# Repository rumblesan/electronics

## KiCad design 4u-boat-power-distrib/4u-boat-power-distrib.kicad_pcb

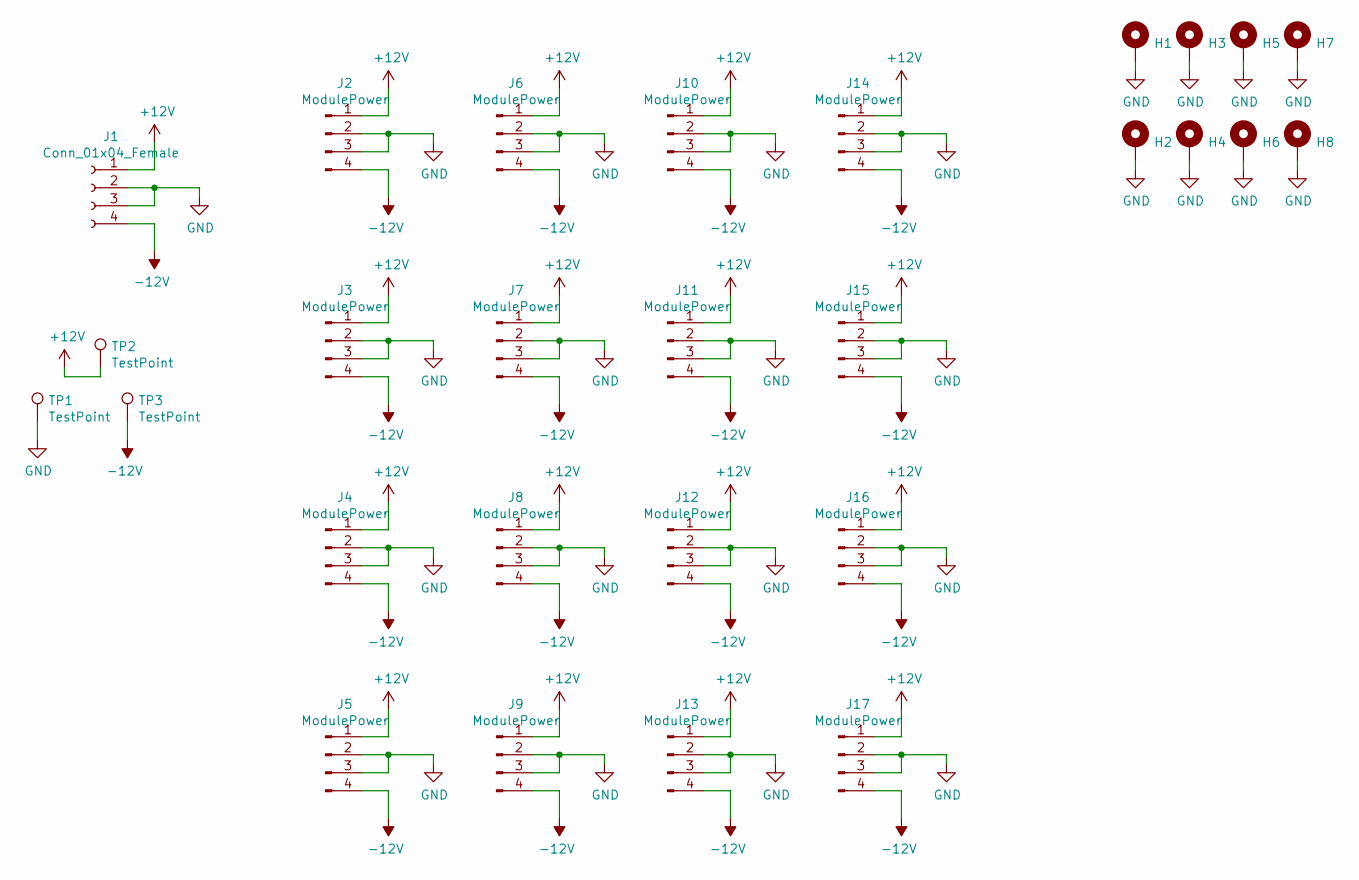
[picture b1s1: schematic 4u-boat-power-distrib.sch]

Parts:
H1, H2, H3, H4, H5, H6, H7, H8: MountingHole_Pad; MountingHole_3.2mm_M3_DIN965_Pad
J1: Conn_01x04_Female; PowerConnection-SolderWire-0.75sqmm_1x04_P4.8mm_D1.25mm_OD2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
J2, J3, J4, J5, J6, J7, J8, J9, J10, J11, J12, J13, J14, J15, J16, J17: ModulePower; KK396_RightAngle_01x04
TP1, TP2, TP3: TestPoint; TestPoint_Loop_D1.80mm_Drill1.0mm_Beaded

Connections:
+12V: J1.1, J2.1, J3.1, J4.1, J5.1, J6.1, J7.1, J8.1, J9.1, J10.1, J11.1, J12.1, J13.1, J14.1, J15.1, J16.1, J17.1, TP2.1
-12V: J1.4, J2.4, J3.4, J4.4, J5.4, J6.4, J7.4, J8.4, J9.4, J10.4, J11.4, J12.4, J13.4, J14.4, J15.4, J16.4, J17.4, TP3.1
GND: H1.1, H2.1, H3.1, H4.1, H5.1, H6.1, H7.1, H8.1, J1.2, J1.3, J2.2, J2.3, J3.2, J3.3, J4.2, J4.3, J5.2, J5.3, J6.2, J6.3, J7.2, J7.3, J8.2, J8.3, J9.2, J9.3, J10.2, J10.3, J11.2, J11.3, J12.2, J12.3, J13.2, J13.3, J14.2, J14.3, J15.2, J15.3, J16.2, J16.3, J17.2, J17.3, TP1.1

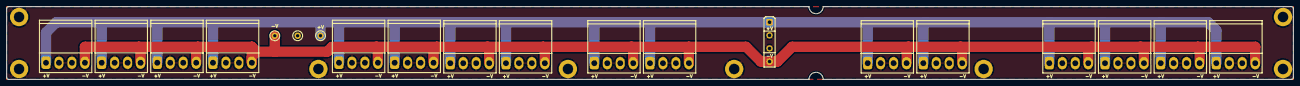
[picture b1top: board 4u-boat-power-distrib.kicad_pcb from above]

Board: 2 copper layers, 393.1 x 22.2 mm, 28 parts (0 on the bottom side), 3 nets.

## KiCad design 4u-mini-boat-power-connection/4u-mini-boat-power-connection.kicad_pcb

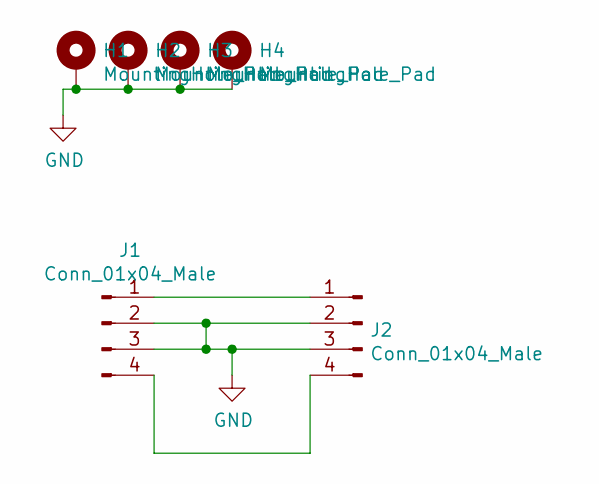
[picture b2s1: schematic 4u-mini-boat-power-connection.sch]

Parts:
H1, H2, H3, H4: MountingHole_Pad; MountingHole_3.2mm_M3_Pad
J1: Conn_01x04_Male; TE_FASTON_250_1217754-1_1x04_P5.08mm_Horizontal
J2: Conn_01x04_Male; Molex_KK-254_AE-6410-04A_1x04_P2.54mm_Vertical

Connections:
GND: H1.1, H2.1, H3.1, H4.1, J1.2, J1.3, J2.2, J2.3
unnamed: J1.1, J2.1
unnamed: J1.4, J2.4

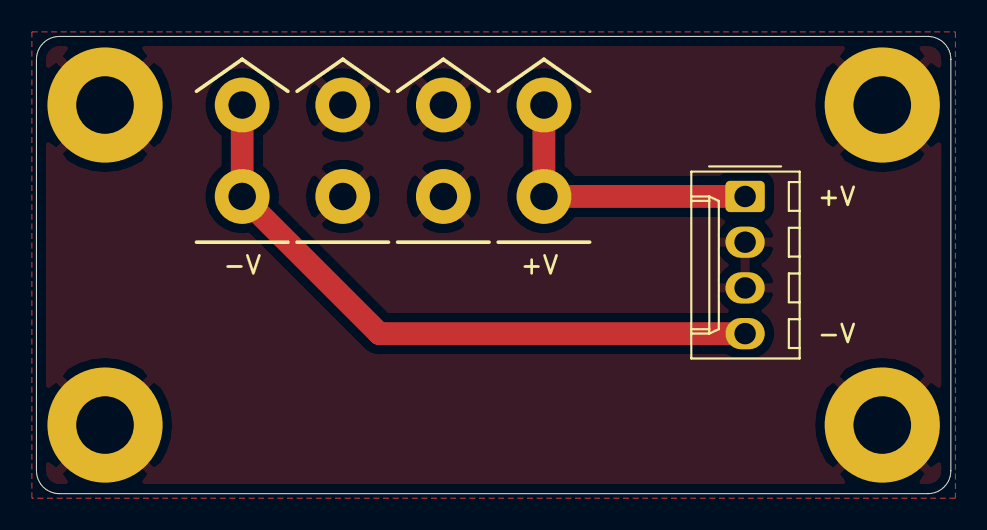
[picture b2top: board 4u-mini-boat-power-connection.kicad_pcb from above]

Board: 2 copper layers, 50.8 x 25.4 mm, 6 parts (0 on the bottom side), 3 nets.

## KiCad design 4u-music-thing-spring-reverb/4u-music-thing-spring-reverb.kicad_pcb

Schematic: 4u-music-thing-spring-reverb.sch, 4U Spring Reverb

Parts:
C1, C2, C10, C12, C13: 10uf; CP_Radial_D5.0mm_P2.50mm
C3: 22uf; CP_Radial_D6.3mm_P2.50mm
C4: 2.2nf; C_Rect_L7.0mm_W2.5mm_P5.00mm
C5, C8, C9: 22pf; C_Rect_L7.0mm_W2.5mm_P5.00mm
C6, C7: 33nf; C_Rect_L7.0mm_W2.5mm_P5.00mm
C11: 3n3f; C_Rect_L7.0mm_W2.5mm_P5.00mm
C14, C15, C16, C17, C18, C19: 100nf; C_Rect_L7.0mm_W2.5mm_P5.00mm
D1, D2: 1n4004; Diode_THT_P7.62mm_Horizontal
J1: IN1; BananaJack_THT_JohnsonCinch_108-09
J2: REV_RETURN; SolderWire-24AWG-0.2sqmm_1x02_D0.5mm_OD1.1mm_Relief
J3: IN2; BananaJack_THT_JohnsonCinch_108-09
J4: OUT; BananaJack_THT_JohnsonCinch_108-09
J5: REV_SEND; SolderWire-24AWG-0.2sqmm_1x02_D0.5mm_OD1.1mm_Relief
J6: TILT_MAIN; PinSocket_1x03_P2.54mm_Vertical
J7: TILT_CTRL; PinHeader_1x03_P2.54mm_Vertical
J8: Conn_01x04_Male; Molex_KK-254_AE-6410-04A_1x04_P2.54mm_Vertical
J9: MIX_CTRL; PinHeader_1x03_P2.54mm_Vertical
J10: MIX_MAIN; PinSocket_1x03_P2.54mm_Vertical
J11: AUDIO_IO_MAIN; PinSocket_1x04_P2.54mm_Vertical
J12: AUDIO_IO_CTRL; PinHeader_1x04_P2.54mm_Vertical
R1: 4k7; Resistor_THT_L6.3mm_D2.5mm_P10.16mm_Horizontal
R2: 22r; Resistor_THT_L6.3mm_D2.5mm_P10.16mm_Horizontal
R3: 22k; Resistor_THT_L6.3mm_D2.5mm_P10.16mm_Horizontal
R4, R5, R6: 10k; Resistor_THT_L6.3mm_D2.5mm_P10.16mm_Horizontal
R7, R12, R15: 2k2; Resistor_THT_L6.3mm_D2.5mm_P10.16mm_Horizontal
R8, R11: 6k8; Resistor_THT_L6.3mm_D2.5mm_P10.16mm_Horizontal
R9, R10, R16: 100k; Resistor_THT_L6.3mm_D2.5mm_P10.16mm_Horizontal
R13: 330; Resistor_THT_L6.3mm_D2.5mm_P10.16mm_Horizontal
R14: 10k; Potentiometer_THT_Bourns_3306P_Vertical
RV1, RV2: 100k; Potentiometer_Alpha_RD901F-40-00D_Single_Vertical
RV3: 10k; Potentiometer_Alpha_RD901F-40-00D_Single_Vertical
U1, U3: TL072; DIP-8_W7.62mm_Socket
U2: NE5532; DIP-8_W7.62mm_Socket

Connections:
+12V: C12.1, C14.1, C16.1, C18.1, D1.1, U1.8 (V+), U2.8 (V+), U3.8 (V+)
-12V: C13.2, C15.2, C17.2, C19.2, D2.2, U1.4 (V-), U2.4 (V-), U3.4 (V-)
/AUDIO1_IN_CTRL: J12.2, RV1.2
/AUDIO1_IN_MAIN: J11.2, R5.2
/AUDIO2_IN_CTRL: C2.1, J12.3, R16.1
/AUDIO2_IN_MAIN: J11.3, R4.2
/AUDIO_DRY_CTRL: J9.1, RV2.1
/AUDIO_DRY_MAIN: J10.1, U3.1, U3.2 (-)
/AUDIO_MIX: C5.1, R6.1, R7.2, R8.2, U2.1, U3.3 (+)
/AUDIO_MIX_CTRL: J9.2, RV2.2
/AUDIO_MIX_MAIN: J10.2, R9.2
/AUDIO_OUT_CTRL: J4.1, J12.1
/AUDIO_OUT_MAIN: J11.1, R10.1, R13.1
/AUDIO_WET_CTRL: J9.3, RV2.3
/AUDIO_WET_MAIN: C4.1, J10.3, R3.1, U1.7
/TILT_CENTRE_CTRL: J7.3, RV3.2
/TILT_CENTRE_MAIN: C8.2, J6.3, U2.6 (-)
/TILT_HI_CTRL: J7.2, RV3.3
/TILT_HI_MAIN: C6.1, J6.2, R11.2
/TILT_LO_CTRL: J7.1, RV3.1
/TILT_LO_MAIN: C7.2, J6.1, R8.1
GND: C12.2, C13.1, C14.2, C15.1, C16.2, C17.1, C18.2, C19.1, J2.2 (Ext), J8.2, J8.3, J11.4, R1.2, R2.2, R14.3, U2.3 (+), U2.5 (+), U3.5 (+)
GND1: J12.4, R16.2, RV1.1
unnamed: C1.1, RV1.3
unnamed: C1.2, J1.1
unnamed: C2.2, J3.1
unnamed: C3.1, R2.1
unnamed: C3.2, C4.2, R3.2, U1.6 (-)
unnamed: C5.2, R4.1, R5.1, R6.2, U2.2 (-)
unnamed: C6.2, R7.1
unnamed: C7.1, R12.2
unnamed: C8.1, R11.1, R12.1, U1.3 (+), U2.7
unnamed: C9.1, R13.2, U3.7
unnamed: C9.2, R9.1, R10.2, U3.6 (-)
unnamed: C10.1, J5.1 (In), R15.2, U1.2 (-)
unnamed: C10.2, R14.1, R14.2
unnamed: C11.1, J5.2 (Ext), U1.1
unnamed: C11.2, R15.1
unnamed: D1.2, J8.1
unnamed: D2.1, J8.4
unnamed: J2.1 (In), R1.1, U1.5 (+)

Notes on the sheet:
Values for R2: 800r tank: R2 = 2k 150r tank: R2 = 470r or use 10k trimmer
R4 and R6 set recovery level R4 should be smaller than output coil impedance 2250/2575r: R4 = 22r R6 = 22k Increase R6 for stronger output, reduce R6 if circuit distorts even when spring drive is set low

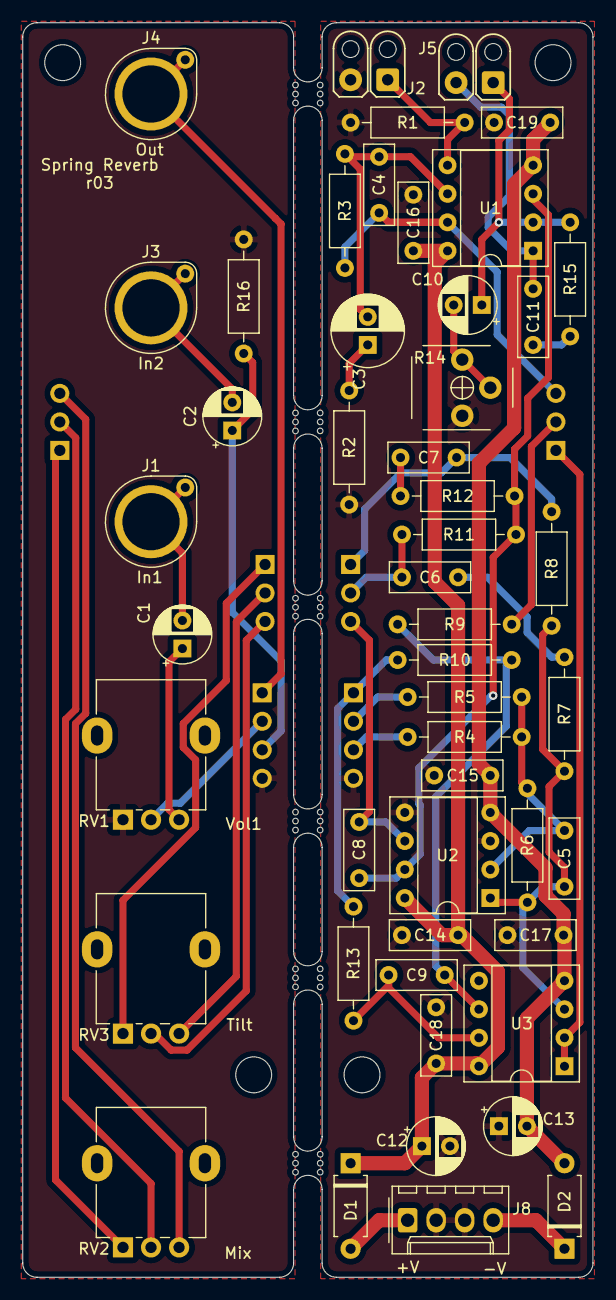
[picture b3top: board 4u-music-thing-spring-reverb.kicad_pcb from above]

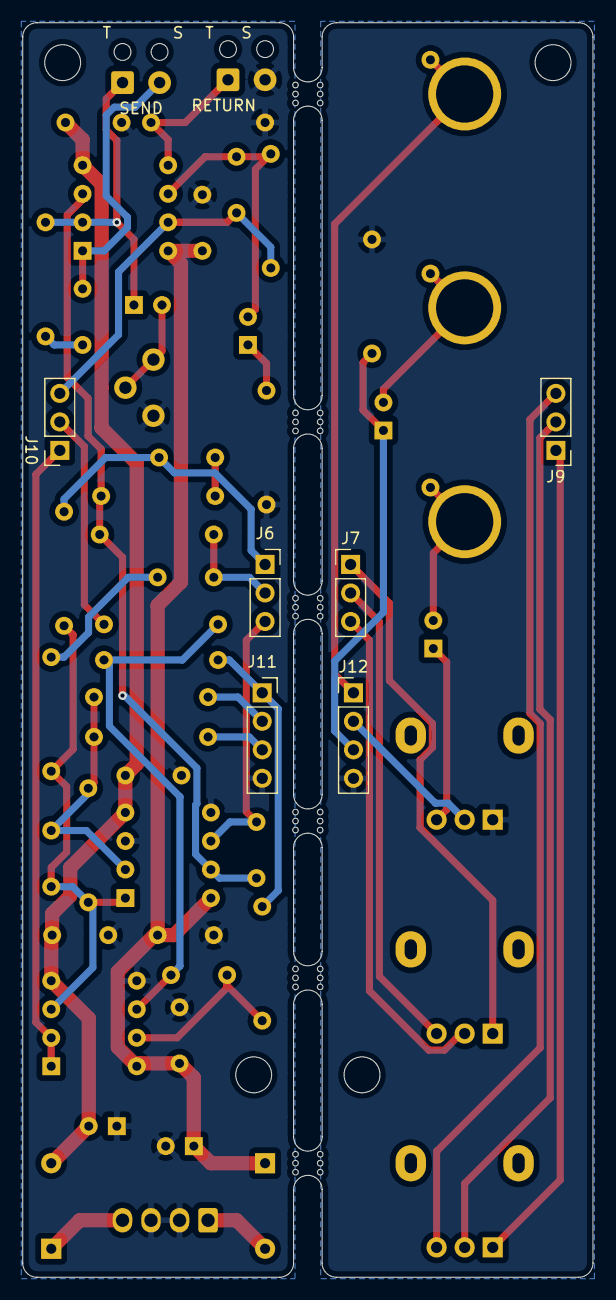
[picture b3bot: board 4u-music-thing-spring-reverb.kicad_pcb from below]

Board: 2 copper layers, 50.8 x 111.8 mm, 61 parts (6 on the bottom side), 41 nets.

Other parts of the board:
mouse-bite-2.54mm-slot, mouse-bite-2.54mm-slot#2, mouse-bite-2.54mm-slot#3, mouse-bite-2.54mm-slot#4, mouse-bite-2.54mm-slot#5, mouse-bite-2.54mm-slot#6: VAL**; mouse-bite-2.54mm-slot

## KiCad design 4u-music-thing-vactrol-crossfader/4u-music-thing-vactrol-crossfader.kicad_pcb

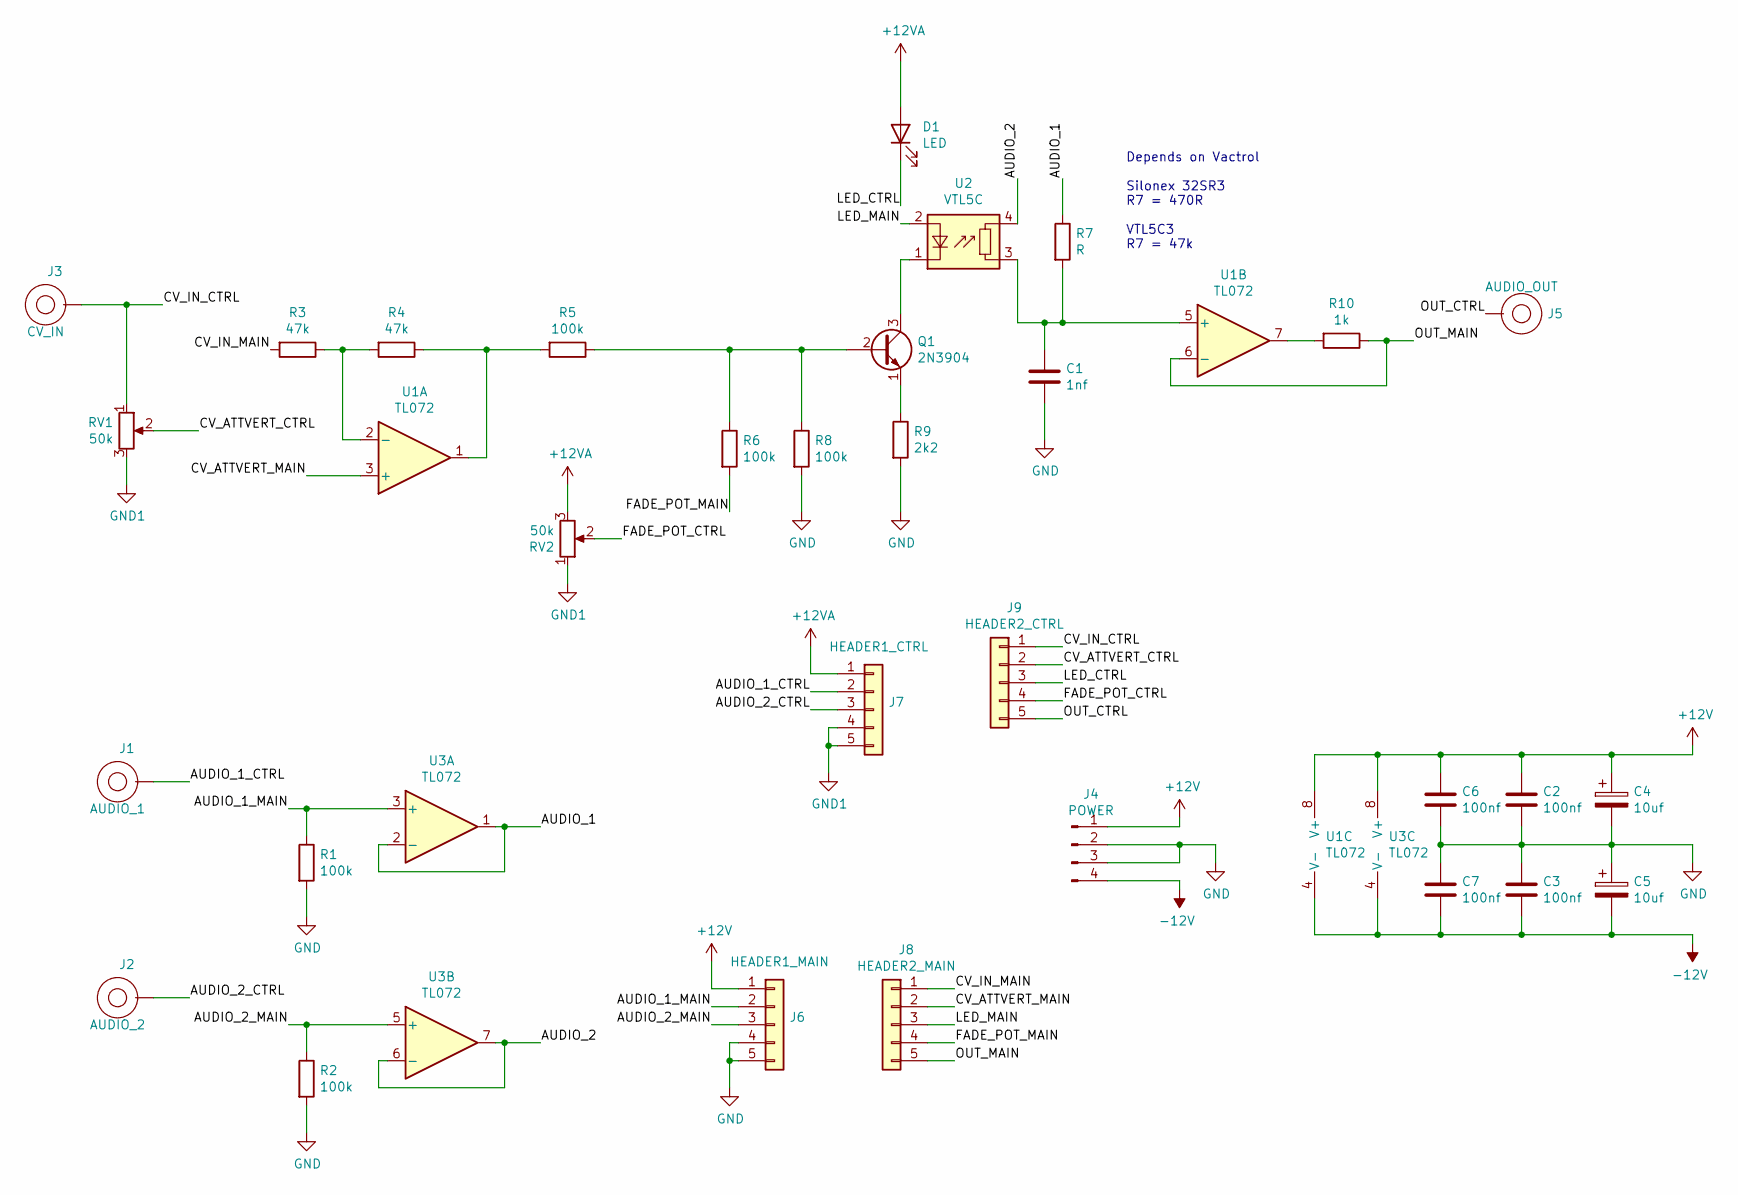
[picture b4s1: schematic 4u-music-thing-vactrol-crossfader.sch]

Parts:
C1: 1nf; C_Rect_L7.0mm_W2.5mm_P5.00mm
C2, C3, C6, C7: 100nf; C_Rect_L7.0mm_W2.5mm_P5.00mm
C4, C5: 10uf; CP_Radial_D5.0mm_P2.50mm
D1: LED; LED_D5.0mm
J1: AUDIO_1; BananaJack_THT_JohnsonCinch_108-09
J2: AUDIO_2; BananaJack_THT_JohnsonCinch_108-09
J3: CV_IN; BananaJack_THT_JohnsonCinch_108-09
J4: POWER; Molex_KK-254_AE-6410-04A_1x04_P2.54mm_Vertical
J5: AUDIO_OUT; BananaJack_THT_JohnsonCinch_108-09
J6: HEADER1_MAIN; PinSocket_1x05_P2.54mm_Vertical
J7: HEADER1_CTRL; PinSocket_1x05_P2.54mm_Vertical
J8: HEADER2_MAIN; PinSocket_1x05_P2.54mm_Vertical
J9: HEADER2_CTRL; PinSocket_1x05_P2.54mm_Vertical
Q1: 2N3904; TO-92_Inline
R1, R2, R5, R6, R8: 100k; Resistor_THT_L6.3mm_D2.5mm_P10.16mm_Horizontal
R3, R4: 47k; Resistor_THT_L6.3mm_D2.5mm_P10.16mm_Horizontal
R7: R; Resistor_THT_L6.3mm_D2.5mm_P10.16mm_Horizontal
R9: 2k2; Resistor_THT_L6.3mm_D2.5mm_P10.16mm_Horizontal
R10: 1k; Resistor_THT_L6.3mm_D2.5mm_P10.16mm_Horizontal
RV1, RV2: 50k; Potentiometer_Alpha_RD901F-40-00D_Single_Vertical
U1, U3: TL072; DIP-8_W7.62mm_Socket
U2: VTL5C; PerkinElmer_VTL5C

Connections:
+12V: C2.1, C4.1, C6.1, J4.1, J6.1, U1.8 (V+), U3.8 (V+)
+12VA: D1.2 (A), J7.1, RV2.3
-12V: C3.2, C5.2, C7.2, J4.4, U1.4 (V-), U3.4 (V-)
/AUDIO_1: R7.1, U3.1, U3.2 (-)
/AUDIO_1_CTRL: J1.1, J7.2
/AUDIO_1_MAIN: J6.2, R1.1, U3.3 (+)
/AUDIO_2: U2.4, U3.6 (-), U3.7
/AUDIO_2_CTRL: J2.1, J7.3
/AUDIO_2_MAIN: J6.3, R2.1, U3.5 (+)
/CV_ATTVERT_CTRL: J9.2, RV1.2
/CV_ATTVERT_MAIN: J8.2, U1.3 (+)
/CV_IN_CTRL: J3.1, J9.1, RV1.1
/CV_IN_MAIN: J8.1, R3.2
/FADE_POT_CTRL: J9.4, RV2.2
/FADE_POT_MAIN: J8.4, R6.2
/LED_CTRL: D1.1 (K), J9.3
/LED_MAIN: J8.3, U2.2 (+)
/OUT_CTRL: J5.1, J9.5
/OUT_MAIN: J8.5, R10.1, U1.6 (-)
GND: C1.2, C2.2, C3.1, C4.2, C5.1, C6.2, C7.1, J4.2, J4.3, J6.4, J6.5, R1.2, R2.2, R8.2, R9.2
GND1: J7.4, J7.5, RV1.3, RV2.1
unnamed: C1.1, R7.2, U1.5 (+), U2.3
unnamed: Q1.1 (E), R9.1
unnamed: Q1.2 (B), R5.1, R6.1, R8.1
unnamed: Q1.3 (C), U2.1 (-)
unnamed: R3.1, R4.2, U1.2 (-)
unnamed: R4.1, R5.2, U1.1
unnamed: R10.2, U1.7

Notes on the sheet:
Depends on Vactrol Silonex 32SR3 R7 = 470R VTL5C3 R7 = 47k

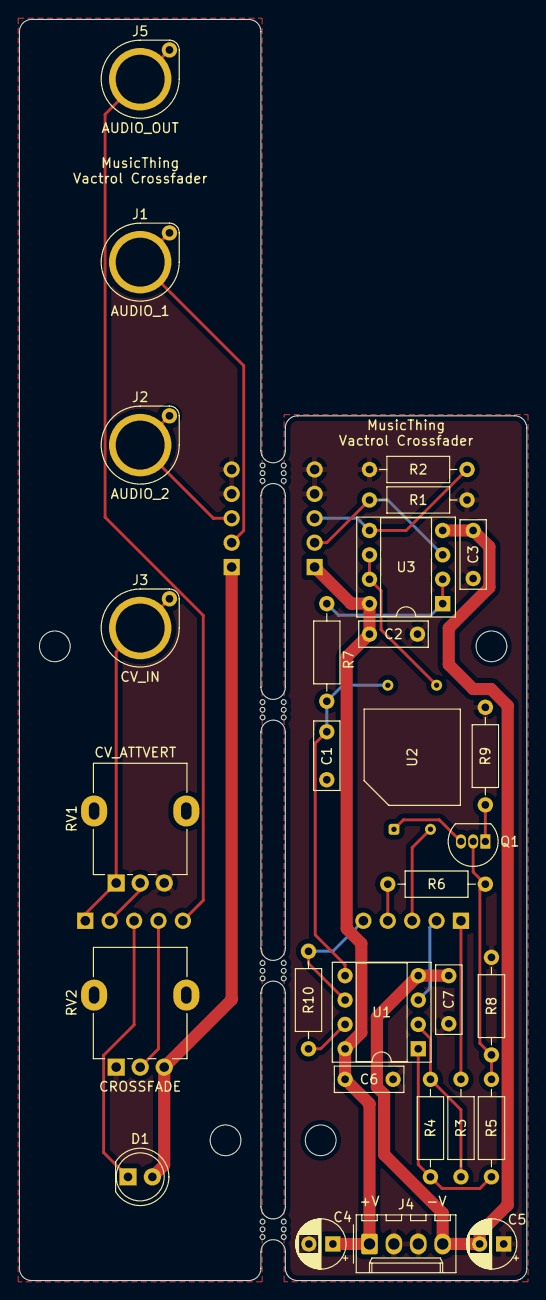
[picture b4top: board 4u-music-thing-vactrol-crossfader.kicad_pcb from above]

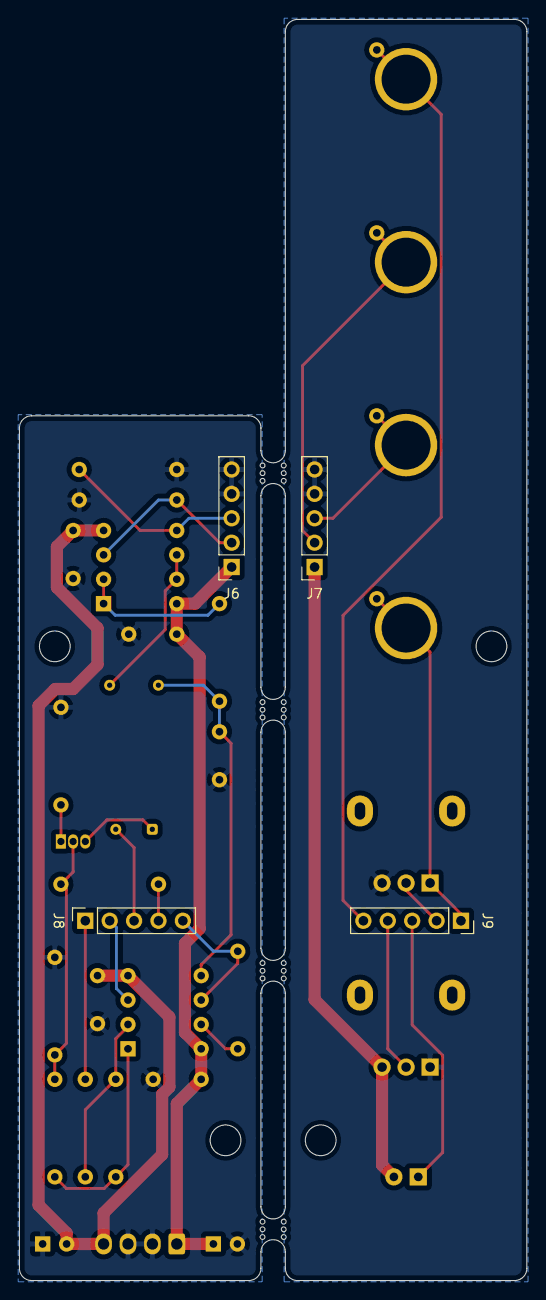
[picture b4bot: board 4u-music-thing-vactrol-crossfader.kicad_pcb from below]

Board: 2 copper layers, 52.8 x 131.3 mm, 37 parts (4 on the bottom side), 28 nets.

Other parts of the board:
mouse-bite-2.54mm-slot, mouse-bite-2.54mm-slot#2, mouse-bite-2.54mm-slot#3, mouse-bite-2.54mm-slot#4: VAL**; mouse-bite-2.54mm-slot

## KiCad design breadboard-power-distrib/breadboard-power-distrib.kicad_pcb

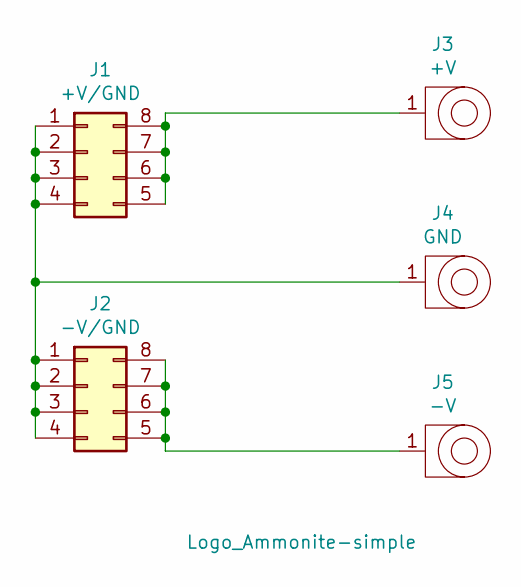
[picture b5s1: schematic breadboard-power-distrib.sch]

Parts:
H1: Logo_Ammonite-simple; Logo_Ammonite-simple_10.4mmx12.0mm
J1: +V/GND; PinHeader_2x4_P2.54mm_Vertical_SMD
J2: -V/GND; PinHeader_2x4_P2.54mm_Vertical_SMD
J3: +V; Deltron_571_PCB_BananaJack
J4: GND; Deltron_571_PCB_BananaJack
J5: -V; Deltron_571_PCB_BananaJack

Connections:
unnamed: J1.1, J1.2, J1.3, J1.4, J2.1, J2.2, J2.3, J2.4, J4.1
unnamed: J1.5, J1.6, J1.7, J1.8, J3.1
unnamed: J2.5, J2.6, J2.7, J2.8, J5.1

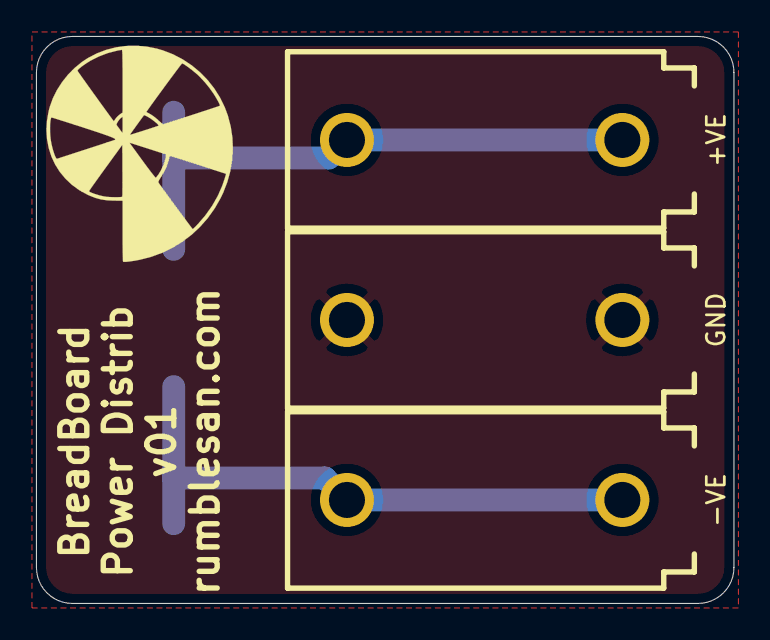
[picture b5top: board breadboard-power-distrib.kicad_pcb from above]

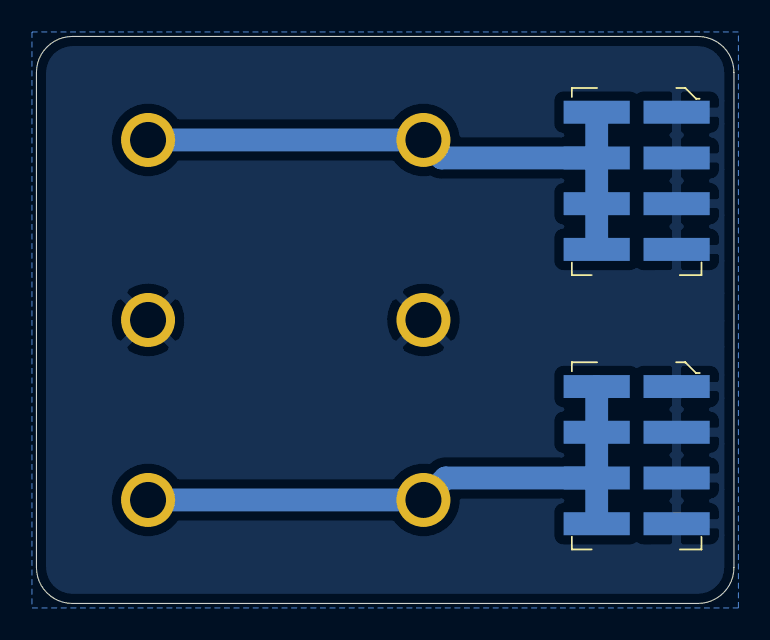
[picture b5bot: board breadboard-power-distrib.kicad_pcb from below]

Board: 2 copper layers, 38.8 x 31.5 mm, 6 parts (2 on the bottom side), 3 nets.

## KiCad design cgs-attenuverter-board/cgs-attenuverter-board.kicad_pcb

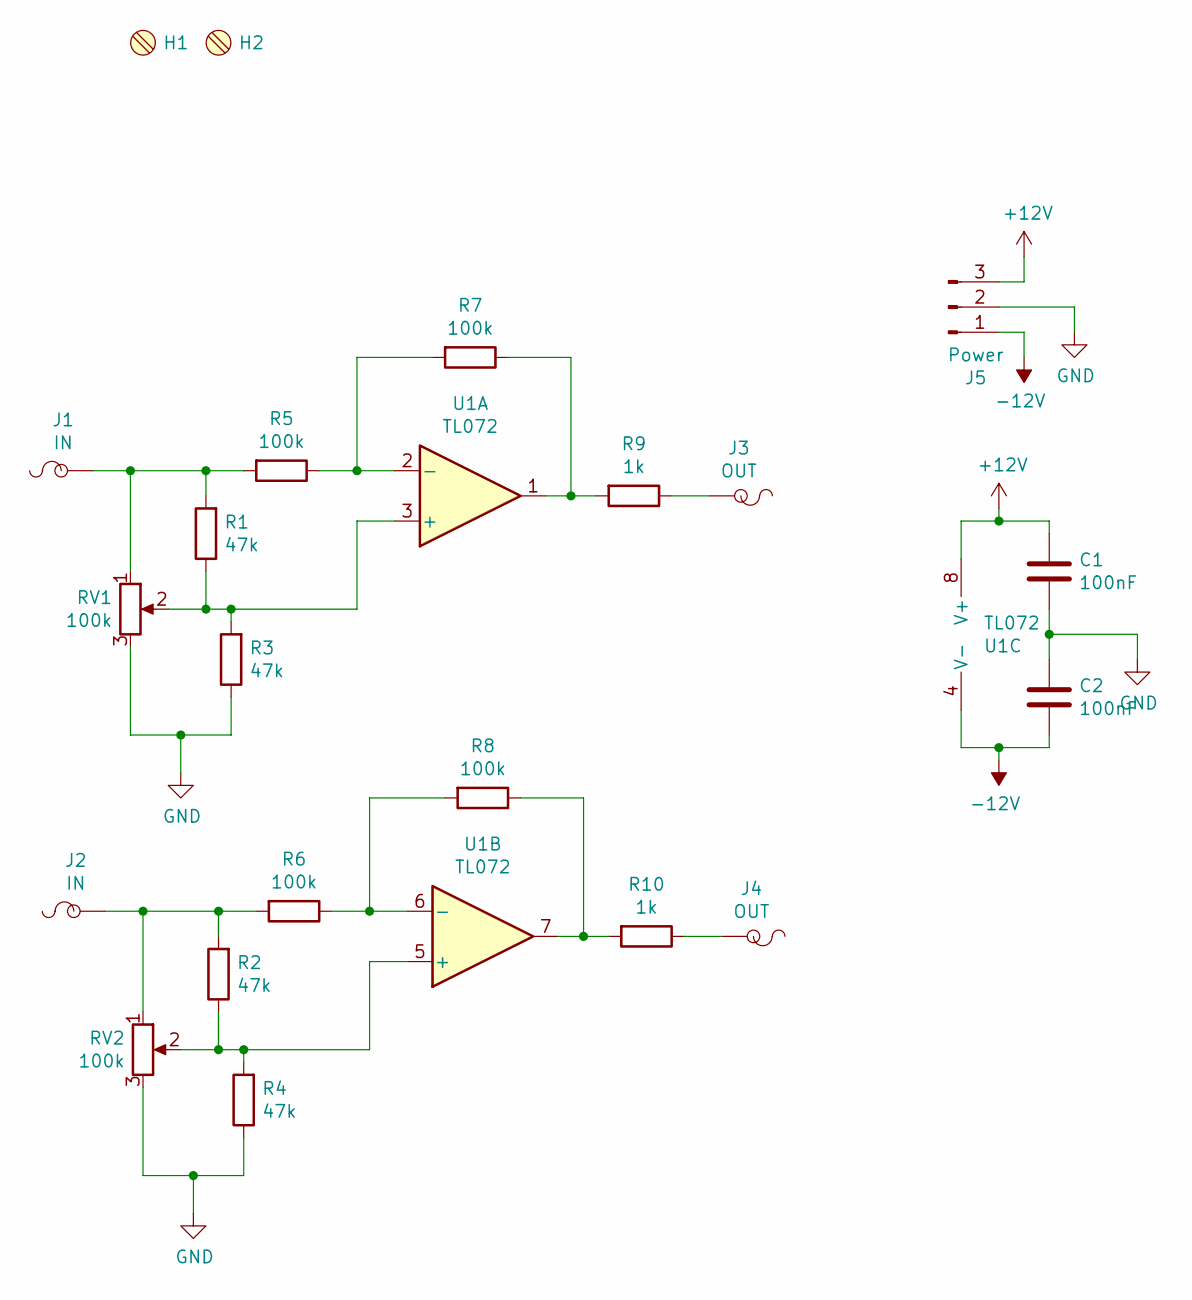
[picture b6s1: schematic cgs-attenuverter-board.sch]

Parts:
C1, C2: 100nF; C_Rect_L7.0mm_W2.5mm_P5.00mm
H1, H2: MountingScrew_M3_Flathead; MountingHole_3.2mm_M3
J1, J2: IN; SolderWire-24AWG-0.2sqmm_1x01_D0.5mm_OD1.1mm_Relief
J3, J4: OUT; SolderWire-24AWG-0.2sqmm_1x01_D0.5mm_OD1.1mm_Relief
J5: Power; SolderWire-24AWG-0.2sqmm_1x03_D0.5mm_OD1.1mm_Relief
R1, R2, R3, R4: 47k; Resistor_THT_L6.3mm_D2.5mm_P10.16mm_Horizontal
R5, R6, R7, R8: 100k; Resistor_THT_L6.3mm_D2.5mm_P10.16mm_Horizontal
R9, R10: 1k; Resistor_THT_L6.3mm_D2.5mm_P10.16mm_Horizontal
RV1, RV2: 100k; SolderWire-24AWG-0.2sqmm_1x03_D0.5mm_OD1.1mm_Relief
U1: TL072; DIP-8_W7.62mm_Socket

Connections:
+12V: C1.1, J5.3, U1.8 (V+)
-12V: C2.2, J5.1, U1.4 (V-)
GND: C1.2, C2.1, J5.2, R3.1, R4.1, RV1.3, RV2.3
unnamed: J1.1, R1.2, R5.2, RV1.1
unnamed: J2.1, R2.2, R6.2, RV2.1
unnamed: J3.1, R9.1
unnamed: J4.1, R10.1
unnamed: R1.1, R3.2, RV1.2, U1.3 (+)
unnamed: R2.1, R4.2, RV2.2, U1.5 (+)
unnamed: R5.1, R7.2, U1.2 (-)
unnamed: R6.1, R8.2, U1.6 (-)
unnamed: R7.1, R9.2, U1.1
unnamed: R8.1, R10.2, U1.7

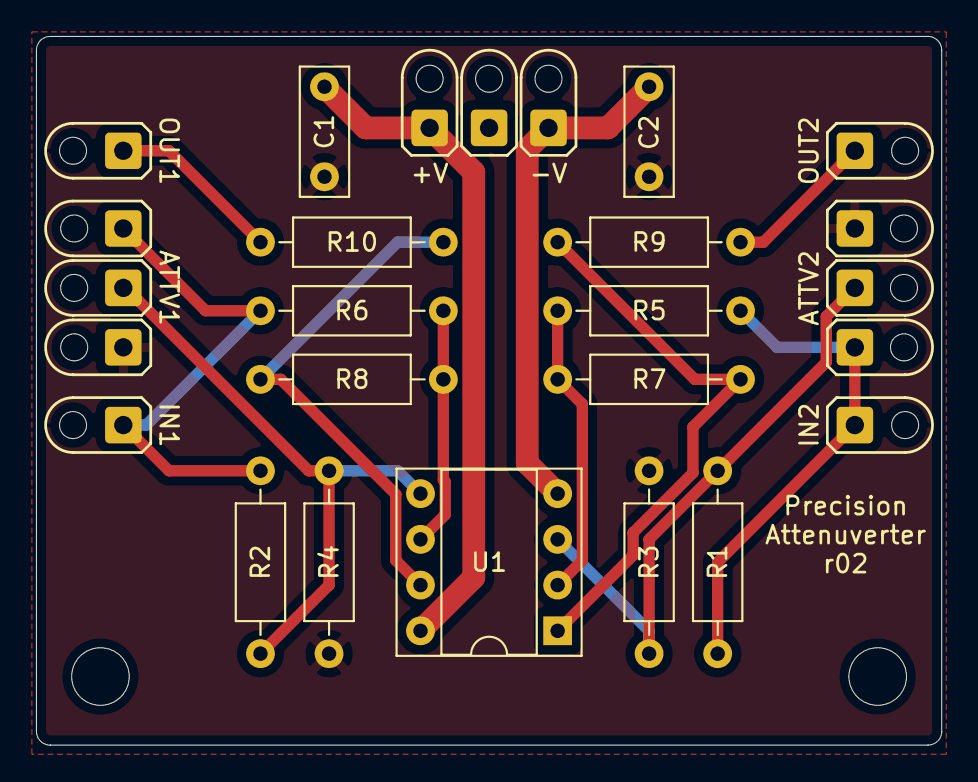
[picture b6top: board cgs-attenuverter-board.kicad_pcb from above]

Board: 2 copper layers, 50.3 x 39.4 mm, 22 parts (0 on the bottom side), 13 nets.

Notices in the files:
4u-mini-boat-power-connection/4u-mini-boat-power-connection.sch:
creativecommons.org/licenses/by/4.0
License: CC BY 4.0
